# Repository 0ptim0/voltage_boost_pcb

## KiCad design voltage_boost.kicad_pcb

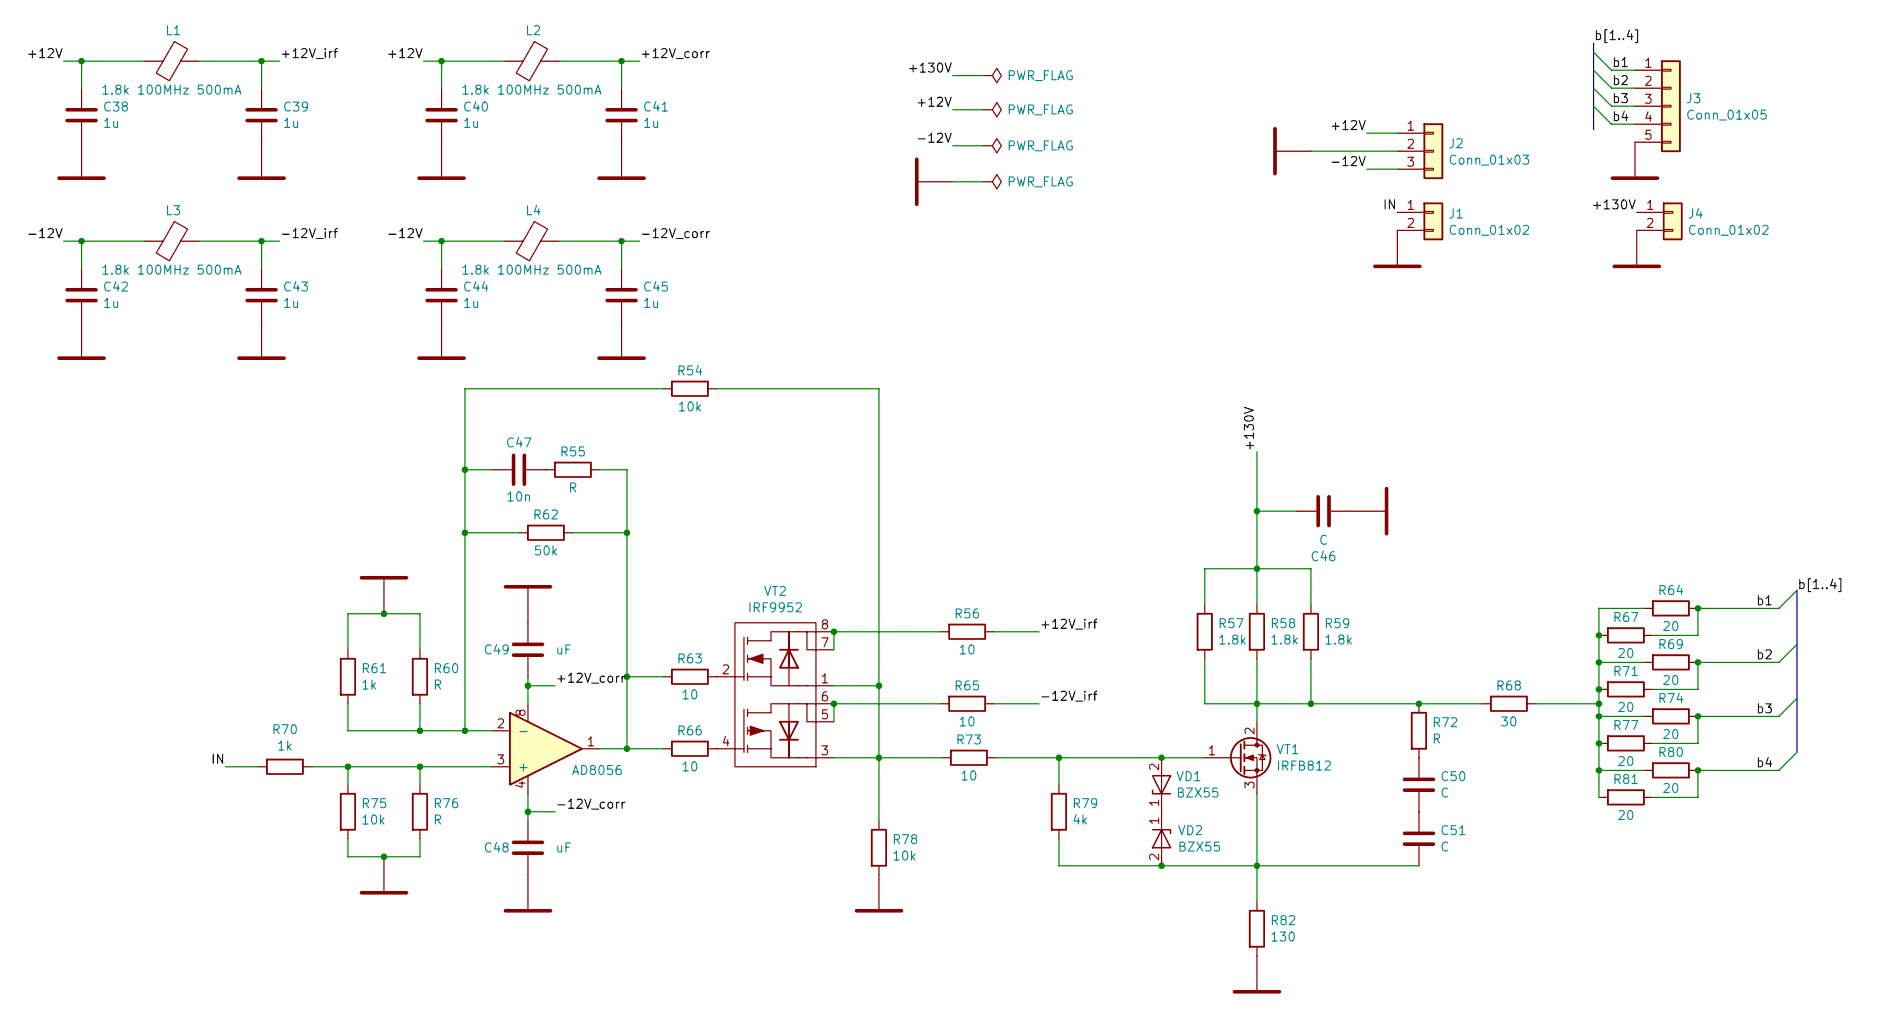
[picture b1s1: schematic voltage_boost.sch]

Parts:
C38, C39, C40, C41, C42, C43, C44, C45: 1u; C_0603_1608Metric
C46: C; CP_Radial_D10.0mm_P5.00mm
C47: 10n; C_0603_1608Metric
C48, C49: uF; C_0603_1608Metric
C50, C51: C; C_Rect_L7.0mm_W4.5mm_P5.00mm
DA1: AD8056; SOIC-8_3.9x4.9mm_P1.27mm
J1, J4: Conn_01x02; PinHeader_1x02_P2.54mm_Vertical
J2: Conn_01x03; PinHeader_1x03_P2.54mm_Vertical
J3: Conn_01x05; PinHeader_1x05_P2.54mm_Vertical
L1, L2, L3, L4: 1.8k 100MHz 500mA; L_0805_2012Metric
R54, R75: 10k; R_0603_1608Metric
R55, R60, R76: R; R_0603_1608Metric
R56, R65: 10; R_1206_3216Metric
R57, R58, R59: 1.8k; R_Axial_DIN0617_L17.0mm_D6.0mm_P25.40mm_Horizontal
R61, R70: 1k; R_0603_1608Metric
R62: 50k; R_0603_1608Metric
R63, R66: 10; R_0603_1608Metric
R64, R67, R69, R71, R74, R77, R80, R81: 20; R_0603_1608Metric
R68: 30; R_Axial_DIN0617_L17.0mm_D6.0mm_P25.40mm_Horizontal
R72: R; R_Axial_DIN0207_L6.3mm_D2.5mm_P15.24mm_Horizontal
R73: 10; R_Axial_DIN0309_L9.0mm_D3.2mm_P15.24mm_Horizontal
R78: 10k; R_Axial_DIN0207_L6.3mm_D2.5mm_P15.24mm_Horizontal
R79: 4k; R_Axial_DIN0207_L6.3mm_D2.5mm_P15.24mm_Horizontal
R82: 130; R_Axial_DIN0617_L17.0mm_D6.0mm_P25.40mm_Horizontal
VD1, VD2: BZX55; D_DO-35_SOD27_P10.16mm_Horizontal
VT1: IRFB812; TO-220-3_Vertical
VT2: IRF9952; SOIC-8_3.9x4.9mm_P1.27mm

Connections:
/+12V: C38.1, C40.1, J2.1, L1.2, L2.2
/+12V_corr: C41.1, C49.1, DA1.8, L2.1
/+12V_irf: C39.1, L1.1, R56.1
/+130V: C46.1, J4.1, R57.1, R58.1, R59.1
/-12V: C42.1, C44.1, J2.3, L3.2, L4.2
/-12V_corr: C45.1, C48.1, DA1.4, L4.1
/-12V_irf: C43.1, L3.1, R65.1
/IN: J1.1, R70.2
/b1: J3.1, R64.1, R67.1
/b2: J3.2, R69.1, R71.1
/b3: J3.3, R74.1, R77.1
/b4: J3.4, R80.1, R81.1
GND: C38.2, C39.2, C40.2, C41.2, C42.2, C43.2, C44.2, C45.2, C46.2, C48.2, C49.2, J1.2, J2.2, J3.5, J4.2, R60.1, R61.1, R75.2, R76.2, R78.2, R82.2
unnamed: C47.1, DA1.2 (-), R54.2, R60.2, R61.2, R62.2
unnamed: C47.2, R55.2
unnamed: C50.1, R72.2
unnamed: C50.2, C51.1
unnamed: C51.2, R79.2, R82.1, VD2.2, VT1.3 (S)
unnamed: DA1.1, R55.1, R62.1, R63.2, R66.2
unnamed: DA1.3 (+), R70.1, R75.1, R76.1
unnamed: R54.1, R73.2, R78.1, VT2.1, VT2.3
unnamed: R56.2, VT2.7, VT2.8
unnamed: R57.2, R58.2, R59.2, R68.2, R72.1, VT1.2 (D)
unnamed: R63.1, VT2.2
unnamed: R64.2, R67.2, R68.1, R69.2, R71.2, R74.2, R77.2, R80.2, R81.2
unnamed: R65.2, VT2.5, VT2.6
unnamed: R66.1, VT2.4
unnamed: R73.1, R79.1, VD1.2, VT1.1 (G)
unnamed: VD1.1, VD2.1

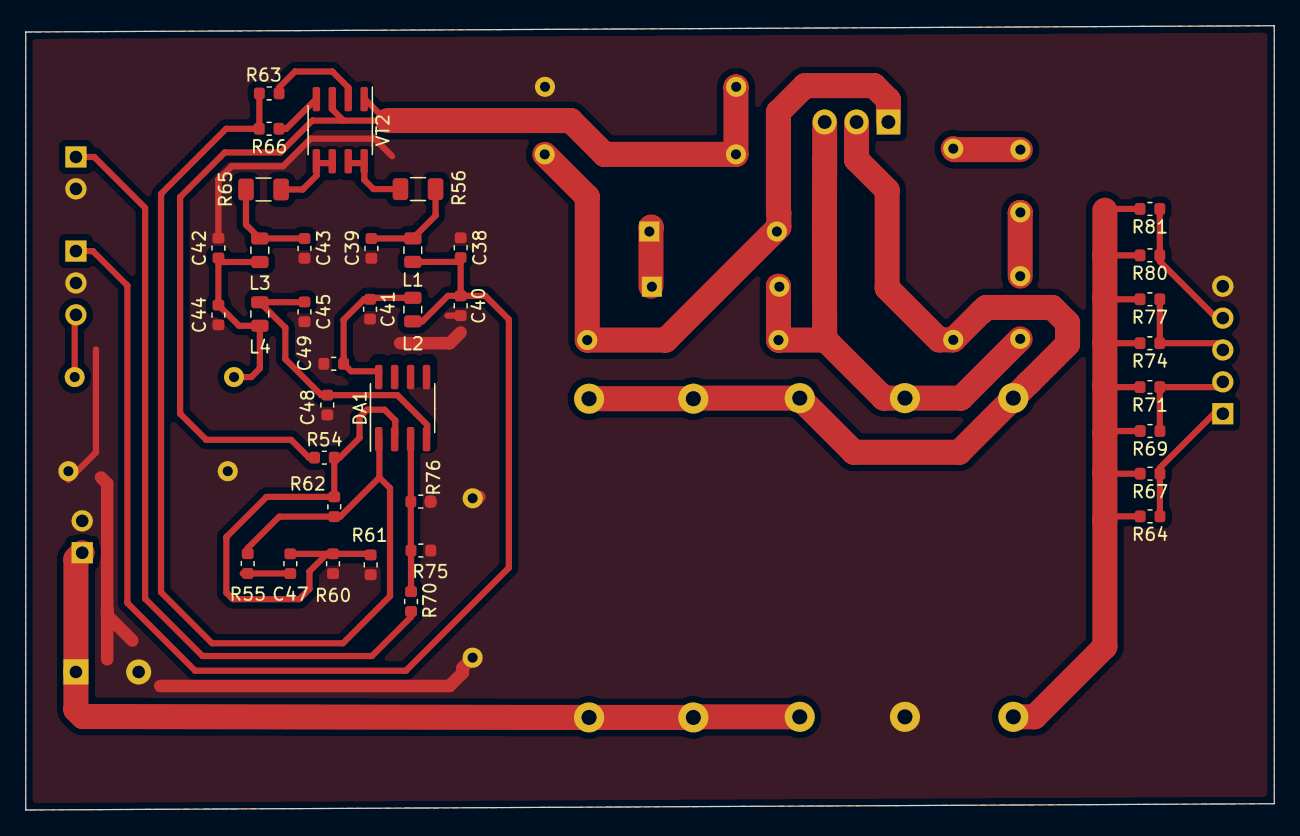
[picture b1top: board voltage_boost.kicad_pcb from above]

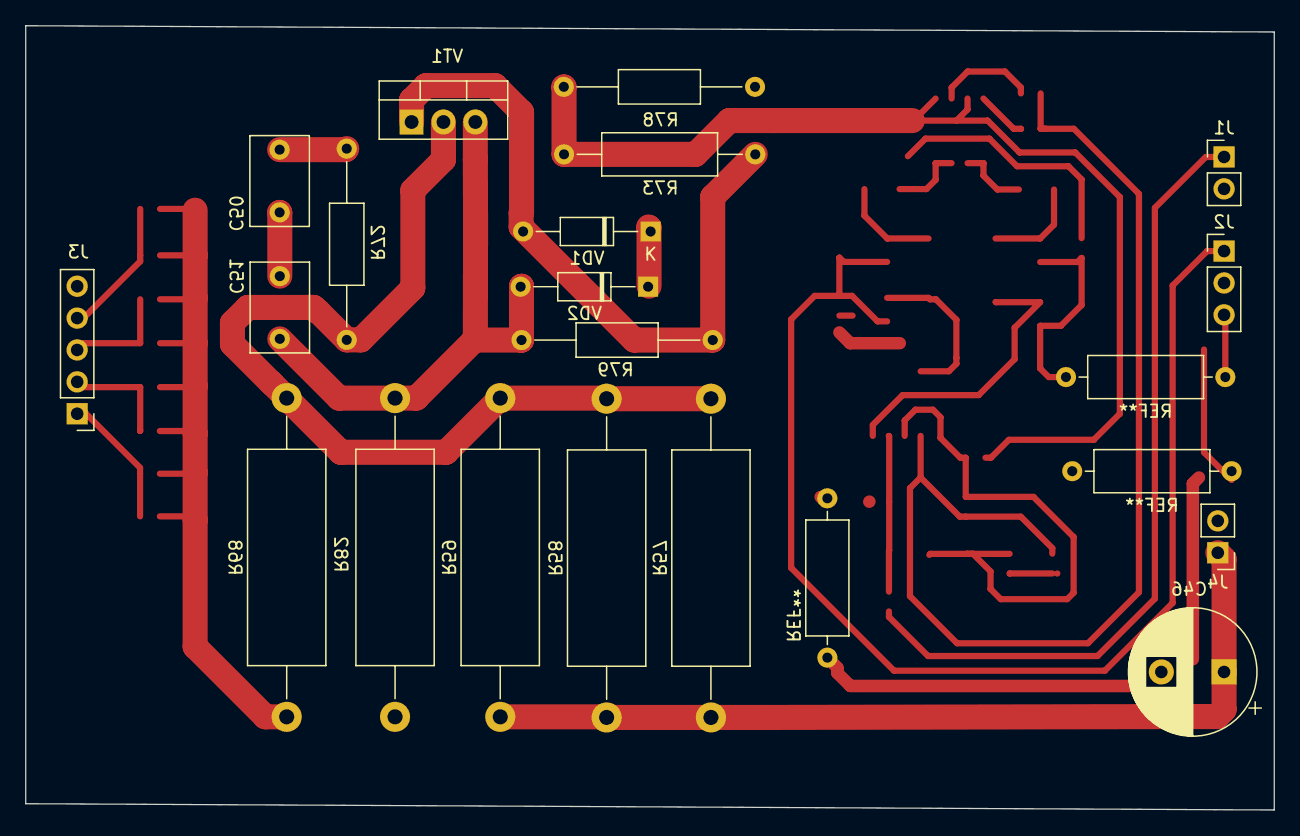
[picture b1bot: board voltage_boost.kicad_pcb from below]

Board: 2 copper layers, 99.5 x 62.5 mm, 56 parts (19 on the bottom side), 29 nets.

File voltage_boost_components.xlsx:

Ref | Value | Footprint
C38 | 1u | Capacitor_SMD:C_0603_1608Metric
C39 | 1u | Capacitor_SMD:C_0603_1608Metric
C40 | 1u | Capacitor_SMD:C_0603_1608Metric
C41 | 1u | Capacitor_SMD:C_0603_1608Metric
C42 | 1u | Capacitor_SMD:C_0603_1608Metric
C43 | 1u | Capacitor_SMD:C_0603_1608Metric
C44 | 1u | Capacitor_SMD:C_0603_1608Metric
C45 | 1u | Capacitor_SMD:C_0603_1608Metric
C46 | C | Capacitor_THT:CP_Radial_D26.0mm_P10.00mm_SnapIn
C47 | 10n | Capacitor_SMD:C_0603_1608Metric
C48 | uF | Capacitor_SMD:C_0603_1608Metric
C49 | uF | Capacitor_SMD:C_0603_1608Metric
C50 | C | Capacitor_THT:CP_Radial_D26.0mm_P10.00mm_SnapIn
C51 | C | Capacitor_THT:CP_Radial_D26.0mm_P10.00mm_SnapIn
DA5 | AD8056 | Package_SO:SO-8_3.9x4.9mm_P1.27mm
L1 | 1.8k 100MHz 500mA | Inductor_SMD:L_0603_1608Metric
L2 | 1.8k 100MHz 500mA | Inductor_SMD:L_0603_1608Metric
L3 | 1.8k 100MHz 500mA | Inductor_SMD:L_0603_1608Metric
L4 | 1.8k 100MHz 500mA | Inductor_SMD:L_0603_1608Metric
Q2 | IRF9952 | Package_SO:SO-8_3.9x4.9mm_P1.27mm
R54 | 10k | Resistor_SMD:R_0603_1608Metric
R55 | R | Resistor_SMD:R_0603_1608Metric
R56 | 10 | Resistor_THT:R_Axial_DIN0309_L9.0mm_D3.2mm_P15.24mm_Horizontal
R57 | 1.8k | Resistor_THT:R_Axial_DIN0617_L17.0mm_D6.0mm_P30.48mm_Horizontal
R58 | 1.8k | Resistor_THT:R_Axial_DIN0617_L17.0mm_D6.0mm_P30.48mm_Horizontal
R59 | 1.8k | Resistor_THT:R_Axial_DIN0617_L17.0mm_D6.0mm_P30.48mm_Horizontal
R60 | R | Resistor_SMD:R_0603_1608Metric
R61 | 10k | Resistor_SMD:R_0603_1608Metric
R62 | 50k | Resistor_SMD:R_0603_1608Metric
R63 | 10 | Resistor_SMD:R_0603_1608Metric
R64 | 20 | Resistor_THT:R_Axial_DIN0309_L9.0mm_D3.2mm_P15.24mm_Horizontal
R65 | 10 | Resistor_THT:R_Axial_DIN0309_L9.0mm_D3.2mm_P15.24mm_Horizontal
R66 | 10 | Resistor_SMD:R_0603_1608Metric
R67 | 20 | Resistor_THT:R_Axial_DIN0309_L9.0mm_D3.2mm_P15.24mm_Horizontal
R68 | 30 | Resistor_THT:R_Axial_DIN0617_L17.0mm_D6.0mm_P20.32mm_Horizontal
R69 | 20 | Resistor_THT:R_Axial_DIN0309_L9.0mm_D3.2mm_P15.24mm_Horizontal
R70 | 1k | Resistor_SMD:R_0603_1608Metric
R71 | 20 | Resistor_THT:R_Axial_DIN0309_L9.0mm_D3.2mm_P15.24mm_Horizontal
R72 | R | Resistor_THT:R_Axial_DIN0617_L17.0mm_D6.0mm_P20.32mm_Horizontal
R73 | 10 | Resistor_THT:R_Axial_DIN0309_L9.0mm_D3.2mm_P15.24mm_Horizontal
R74 | 20 | Resistor_THT:R_Axial_DIN0309_L9.0mm_D3.2mm_P15.24mm_Horizontal
R75 | 10k | Resistor_SMD:R_0603_1608Metric
R76 | R | Resistor_SMD:R_0603_1608Metric
R77 | 20 | Resistor_THT:R_Axial_DIN0309_L9.0mm_D3.2mm_P15.24mm_Horizontal
R78 | 10k | Resistor_SMD:R_0603_1608Metric
R79 | 4k | Resistor_SMD:R_0603_1608Metric
R80 | 20 | Resistor_THT:R_Axial_DIN0309_L9.0mm_D3.2mm_P15.24mm_Horizontal
R81 | 20 | Resistor_THT:R_Axial_DIN0309_L9.0mm_D3.2mm_P15.24mm_Horizontal
R82 | 130 | Resistor_THT:R_Axial_DIN0617_L17.0mm_D6.0mm_P20.32mm_Horizontal
VD10 | BZX55 | Diode_THT:D_DO-35_SOD27_P10.16mm_Horizontal
VD11 | BZX55 | Diode_THT:D_DO-35_SOD27_P10.16mm_Horizontal
VT1 | IRFB812 | Package_TO_SOT_THT:TO-220-3_Vertical

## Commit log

2021-03-05 voltage boost
2021-03-05 transfered library
2021-03-05 added readme and screenshots
